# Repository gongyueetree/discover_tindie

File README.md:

# Tindie Resources — Production System

> **Discover page, four tabs:** Resources (this app, unchanged) · Components · Open hardware · PCB planner.
> Component, design and knowledge-graph data come from the ezplm_partdata Partner API (signed, server-side);
> CAD drawing and project parsing use engines from eelib. **See [DISCOVER_TABS.md](DISCOVER_TABS.md)** (中文) for
> architecture, environment variables (`PARTDATA_API_BASE` / `PARTDATA_API_KEY` / `PARTDATA_API_SECRET`,
> `MAKER_GITHUB_TOKEN`), local integration testing and the go-live checklist. `npm test` runs all offline checks.

A real, database-backed Next.js app for the Tindie "Resources" section:

- **Public site**: home (Top 12 daily discoveries), `/archive` (by day), `/directory` (50 curated resources)
- **Admin** (`/admin`, login-protected): discovery inbox → approve/publish, resource directory + broken-link re-verify, source pause/resume, submission moderation, dashboard
- **Auth**: email + password (Auth.js + Drizzle adapter), role-based (`user` / `editor` / `admin`)
- **AI pipeline**: daily Vercel Cron → `runDiscoveryPipeline()` inserts new candidates as `needs_review`. Currently a **mock** with two clearly-marked integration points (real sources + Claude API).
- **Persistence**: real Postgres — saves, comments, submissions, approvals are shared across all users and devices (not localStorage).

## Stack
Next.js 14 (App Router) · Vercel Postgres · Drizzle ORM · Auth.js v5 · Tailwind · Vercel Cron.

---

## Deploy to Vercel (step by step)

### 1. Push to GitHub
Create a repo and push this folder (or upload the files via GitHub's web "Add file → Upload files").

### 2. Import into Vercel
- vercel.com → **Add New… → Project** → import the repo.
- Framework preset: **Next.js** (auto-detected). Leave build settings default.

### 3. Add a database
- In the project → **Storage → Create → Postgres** (Vercel Postgres).
- Vercel automatically injects `POSTGRES_URL` into the project's environment.

### 4. Set environment variables
Project → **Settings → Environment Variables** (see `.env.example`):

| Variable | Value |
|---|---|
| `AUTH_SECRET` | run `openssl rand -base64 32` |
| `CRON_SECRET` | any long random string |
| `SEED_ADMIN_EMAIL` | e.g. `you@yourdomain.com` |
| `SEED_ADMIN_PASSWORD` | a strong password |

(`POSTGRES_URL` is already set by step 3. `ANTHROPIC_API_KEY` only later, when wiring real AI.)

### 5. Create the tables + seed data
Run locally against the production DB (pull the env first), **or** from any machine:

```bash
npm install
# put the Vercel POSTGRES_URL + the vars above into a local .env
npm run db:migrate   # creates all 11 tables
npm run db:seed      # 50 resources, 7 sources, ~12 published + 4 review-queue discoveries, admin user
```

Tip: `vercel env pull .env` copies the project's env vars locally.

### 6. Done
- Public: `https://<project>.vercel.app/`
- Admin: `https://<project>.vercel.app/admin` → redirected to `/login`. Sign in with the seed admin.
- Daily cron is configured in `vercel.json` (05:00 UTC) and calls `/api/cron/discover`.

---

## How the daily pipeline works (and how to make it real)

`src/lib/pipeline.ts` runs on a schedule and:
1. `fetchCandidates()` — **MOCK** today (shuffles a sample pool).
2. `scoreCandidate()` — relevance/novelty/trust scoring.
3. `summarize()` — **MOCK** today (returns canned text).
4. `applyGuardrails()` — diversity caps (≤3 per category, ≤2 per source, target 12).
5. Inserts as `status: 'needs_review'` for one-click human approval in the admin.

**To go live, replace two functions (signatures stay the same):**
- **INTEGRATION POINT 1 — `fetchCandidates()`**: pull from real RSS/API/crawl of each active source. Respect each source's ToS; only use OG/press/repo-licensed images; record `imageLicense`.
- **INTEGRATION POINT 2 — `summarize()`**: call the Anthropic API with `ANTHROPIC_API_KEY` to generate an **original** summary + "why it matters" (the commented example uses `claude-haiku-4-5-20251001`). Never copy source text.

Nothing else needs to change — approvals, archive, and the public feed already read from the DB.

---

## Local development

```bash
npm install
cp .env.example .env   # fill in a local or Vercel POSTGRES_URL + AUTH_SECRET
npm run db:migrate && npm run db:seed
npm run dev            # http://localhost:3000
```

## Roles
- `admin` / `editor` → can open `/admin` and call `/api/admin/*`.
- Everyone else → redirected to `/login`.
Change a user's role directly in the `users` table (`role` column).

## Security notes
- Admin area + admin APIs are enforced in `src/middleware.ts`.
- The cron endpoint requires `Authorization: Bearer $CRON_SECRET` (Vercel Cron sends this automatically when `CRON_SECRET` is set).
- Change the seed admin password after first login.

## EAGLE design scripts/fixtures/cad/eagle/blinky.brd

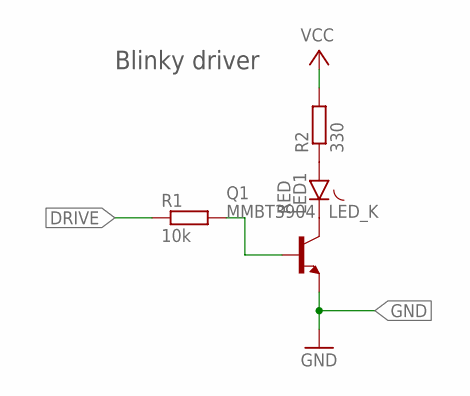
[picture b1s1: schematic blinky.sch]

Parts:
LED1: RED; LED3MM
Q1: MMBT3904; SOT23
R1: 10k; R0603; MPN RC0603FR-0710KL
R2: 330; R0603

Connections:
BASE: Q1.1 (B), R1.2
DRIVE: R1.1
GND: Q1.2 (E)
LED_K: LED1.K (C), Q1.3 (C)
unnamed: LED1.A, R2.1
VCC: R2.2

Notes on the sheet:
Blinky driver

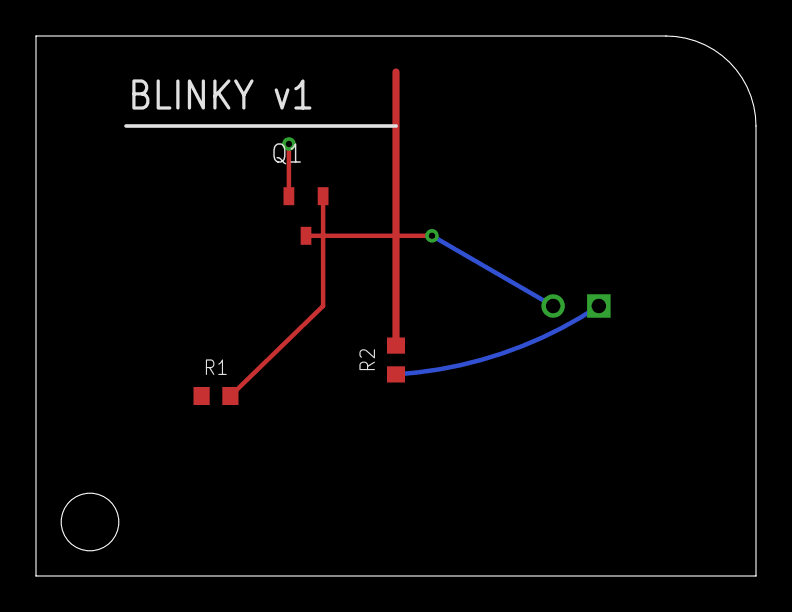
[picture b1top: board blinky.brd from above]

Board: 2 copper layers, 40.0 x 30.0 mm, 4 parts (1 on the bottom side), 3 nets.
